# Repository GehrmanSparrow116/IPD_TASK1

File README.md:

# IPD_TASK1 BY GROUP 28

E077-Sarvesh Hedulkar

E076-Tanish Hangloo

E070-Chaitanya Deorukhkar

E079-Aadit Rajbhar

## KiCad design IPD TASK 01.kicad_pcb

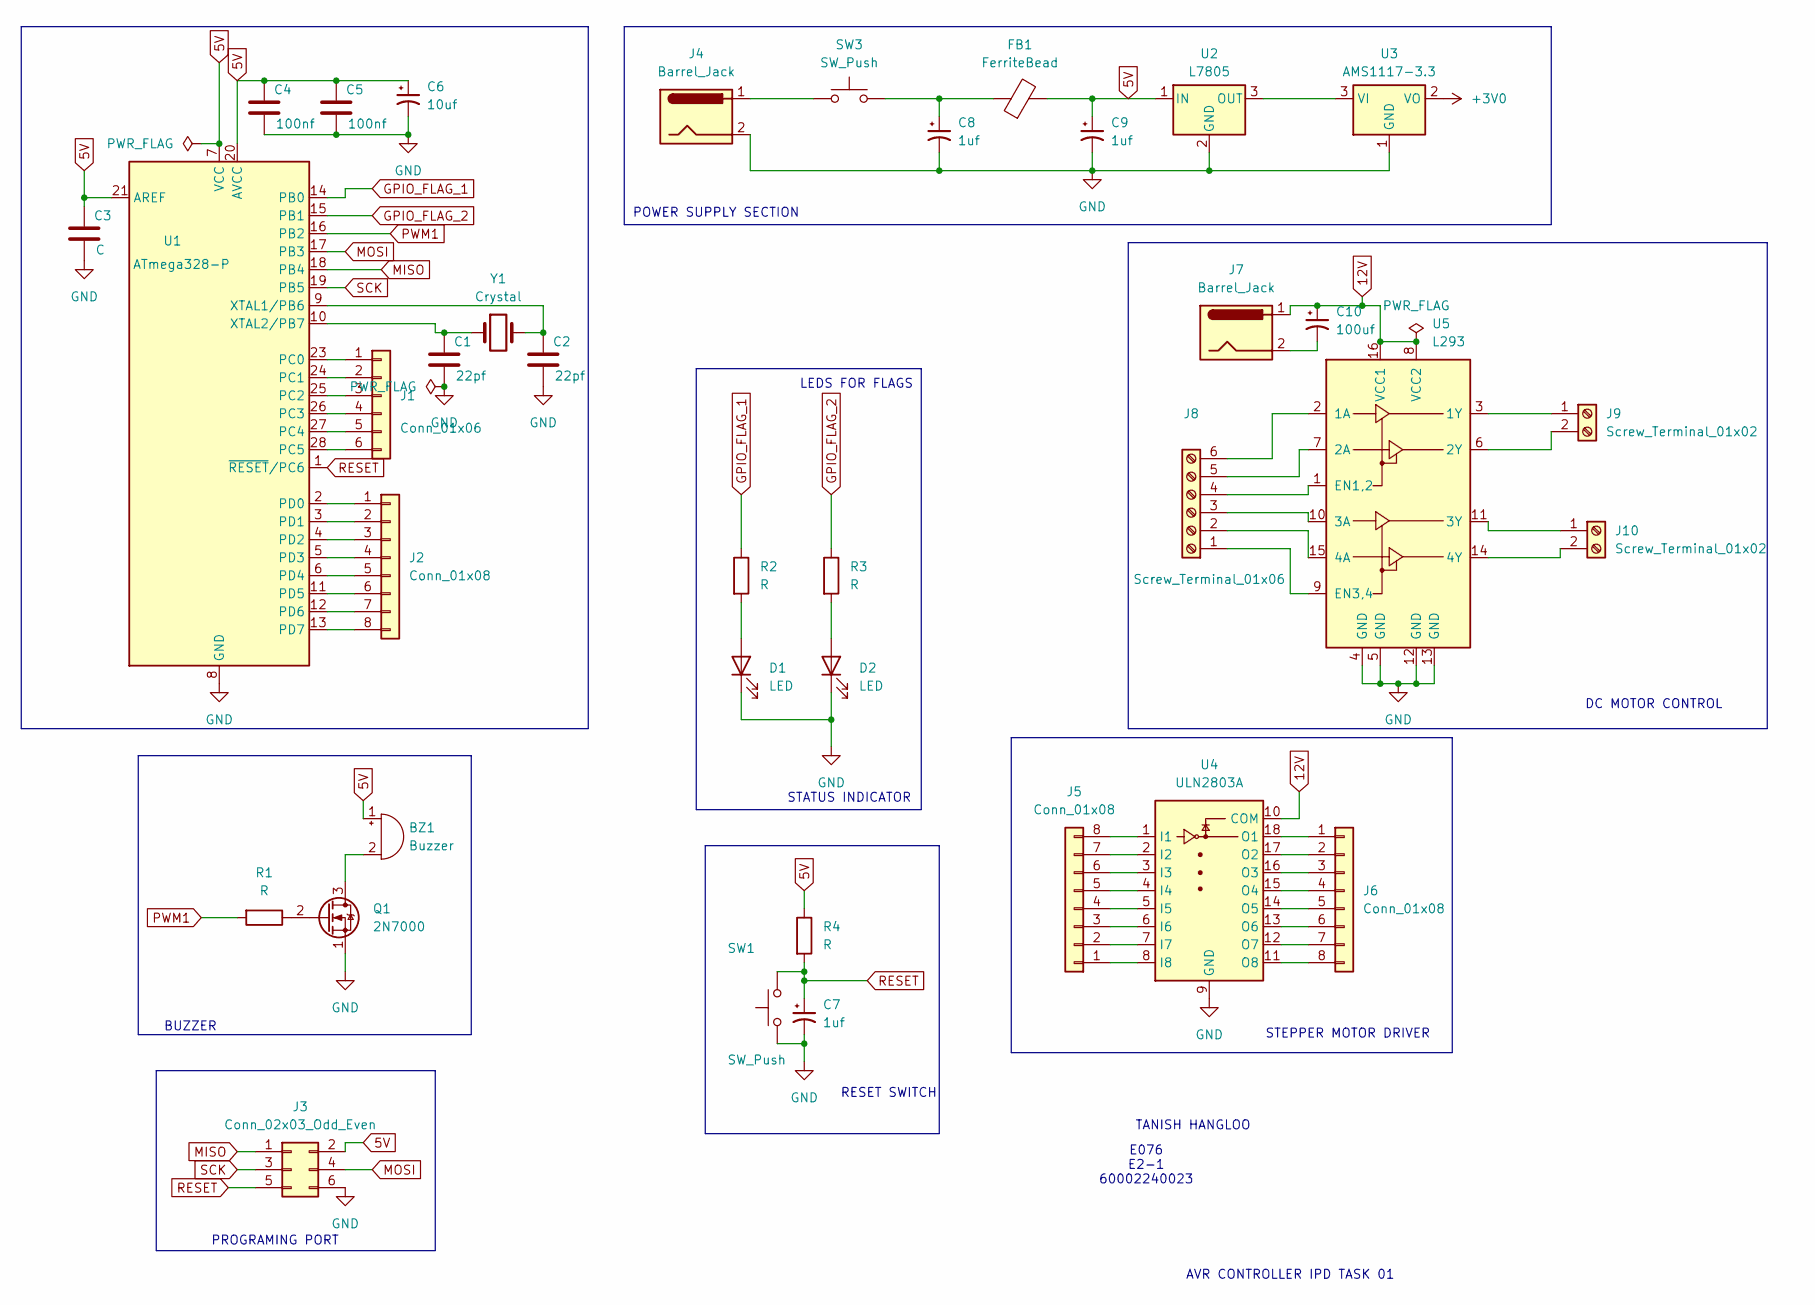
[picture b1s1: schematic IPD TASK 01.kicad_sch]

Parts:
BZ1: Buzzer; PinHeader_1x02_P2.54mm_Vertical
C1, C2: 22pf; C_Disc_D5.0mm_W2.5mm_P5.00mm
C3: C; C_Disc_D5.0mm_W2.5mm_P5.00mm
C4, C5: 100nf; CP_Radial_D5.0mm_P2.50mm
C6: 10uf; CP_Radial_D5.0mm_P2.50mm
C7, C8, C9: 1uf; C_Disc_D5.0mm_W2.5mm_P5.00mm
C10: 100uf; C_Disc_D5.0mm_W2.5mm_P5.00mm
D1, D2: LED; LED_D5.0mm
FB1: FerriteBead; R_Axial_DIN0207_L6.3mm_D2.5mm_P7.62mm_Horizontal
J1: Conn_01x06; PinHeader_1x06_P2.54mm_Vertical
J2, J5, J6: Conn_01x08; PinHeader_1x08_P2.54mm_Vertical
J3: Conn_02x03_Odd_Even; PinHeader_2x03_P2.54mm_Vertical
J4: Barrel_Jack; PinHeader_1x02_P2.54mm_Vertical
J7: Barrel_Jack; TerminalBlock_Phoenix_PT-1,5-2-5.0-H_1x02_P5.00mm_Horizontal
J8: Screw_Terminal_01x06; PinHeader_1x06_P2.54mm_Vertical
J9, J10: Screw_Terminal_01x02; PinHeader_1x02_P2.54mm_Vertical
Q1: 2N7000; TO-92_Inline
R1, R2, R3, R4: R; R_Axial_DIN0207_L6.3mm_D2.5mm_P15.24mm_Horizontal
SW1, SW3: SW_Push; PinHeader_1x02_P2.54mm_Vertical
U1: ATmega328-P; DIP-28_W7.62mm
U2: L7805; TO-220-3_Vertical
U3: AMS1117-3.3; SOT-223-3_TabPin2
U4: ULN2803A; DIP-18_W7.62mm
U5: L293; DIP-16_W7.62mm
Y1: Crystal; Crystal_HC49-U_Vertical

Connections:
5V: BZ1.1 (+), C3.1, C4.1, C5.1, C6.1, C9.1, FB1.2, J3.2, R4.1, U1.7 (VCC), U1.20 (AVCC), U1.21 (AREF), U2.1 (IN)
12V: C10.1, J7.1, U4.10 (COM), U5.8 (VCC2), U5.16 (VCC1)
+3V0: U3.2 (VO)
GND: C1.2, C2.2, C3.2, C4.2, C5.2, C6.2, C7.2, C8.2, C9.2, D1.1 (K), D2.1 (K), J3.6, J4.2, Q1.1 (S), SW1.1, U1.8 (GND), U1.22 (GND), U2.2 (GND), U3.1 (GND), U4.9 (GND), U5.4 (GND), U5.5 (GND), U5.12 (GND), U5.13 (GND)
GPIO_FLAG_1: R2.1, U1.14 (PB0)
GPIO_FLAG_2: R3.1, U1.15 (PB1)
MISO: J3.1, U1.18 (PB4)
MOSI: J3.4, U1.17 (PB3)
unnamed: BZ1.2 (-), Q1.3 (D)
unnamed: C8.1, FB1.1, SW3.2
unnamed: C10.2, J7.2
unnamed: D1.2 (A), R2.2
unnamed: D2.2 (A), R3.2
unnamed: J1.1, U1.23 (PC0)
unnamed: J1.2, U1.24 (PC1)
unnamed: J1.3, U1.25 (PC2)
unnamed: J1.4, U1.26 (PC3)
unnamed: J1.5, U1.27 (PC4)
unnamed: J1.6, U1.28 (PC5)
unnamed: J2.1, U1.2 (PD0)
unnamed: J2.2, U1.3 (PD1)
unnamed: J2.3, U1.4 (PD2)
unnamed: J2.4, U1.5 (PD3)
unnamed: J2.5, U1.6 (PD4)
unnamed: J2.6, U1.11 (PD5)
unnamed: J2.7, U1.12 (PD6)
unnamed: J2.8, U1.13 (PD7)
unnamed: J4.1, SW3.1
unnamed: J5.1, U4.8 (I8)
unnamed: J5.2, U4.7 (I7)
unnamed: J5.3, U4.6 (I6)
unnamed: J5.4, U4.5 (I5)
unnamed: J5.5, U4.4 (I4)
unnamed: J5.6, U4.3 (I3)
unnamed: J5.7, U4.2 (I2)
unnamed: J5.8, U4.1 (I1)
unnamed: J6.1, U4.18 (O1)
unnamed: J6.2, U4.17 (O2)
unnamed: J6.3, U4.16 (O3)
unnamed: J6.4, U4.15 (O4)
unnamed: J6.5, U4.14 (O5)
unnamed: J6.6, U4.13 (O6)
unnamed: J6.7, U4.12 (O7)
unnamed: J6.8, U4.11 (O8)
unnamed: J8.1, U5.9 (EN3,4)
unnamed: J8.2, U5.15 (4A)
unnamed: J8.3, U5.10 (3A)
unnamed: J8.4, U5.1 (EN1,2)
unnamed: J8.5, U5.7 (2A)
unnamed: J8.6, U5.2 (1A)
unnamed: J9.1, U5.3 (1Y)
unnamed: J9.2, U5.6 (2Y)
unnamed: J10.1, U5.11 (3Y)
unnamed: J10.2, U5.14 (4Y)
unnamed: Q1.2 (G), R1.1
unnamed: C2.1, U1.9 (XTAL1/PB6), Y1.2
unnamed: C1.1, U1.10 (XTAL2/PB7), Y1.1
unnamed: U2.3 (OUT), U3.3 (VI)
PWM1: R1.2, U1.16 (PB2)
RESET: C7.1, J3.5, R4.2, SW1.2, U1.1 (~RESET/PC6)
SCK: J3.3, U1.19 (PB5)

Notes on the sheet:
PROGRAMING PORT
DC MOTOR CONTROL
BUZZER
AVR CONTROLLER IPD TASK 01
RESET SWITCH
STEPPER MOTOR DRIVER
STATUS INDICATOR
POWER SUPPLY SECTION
LEDS FOR FLAGS
TANISH HANGLOO
E076 E2-1 60002240023

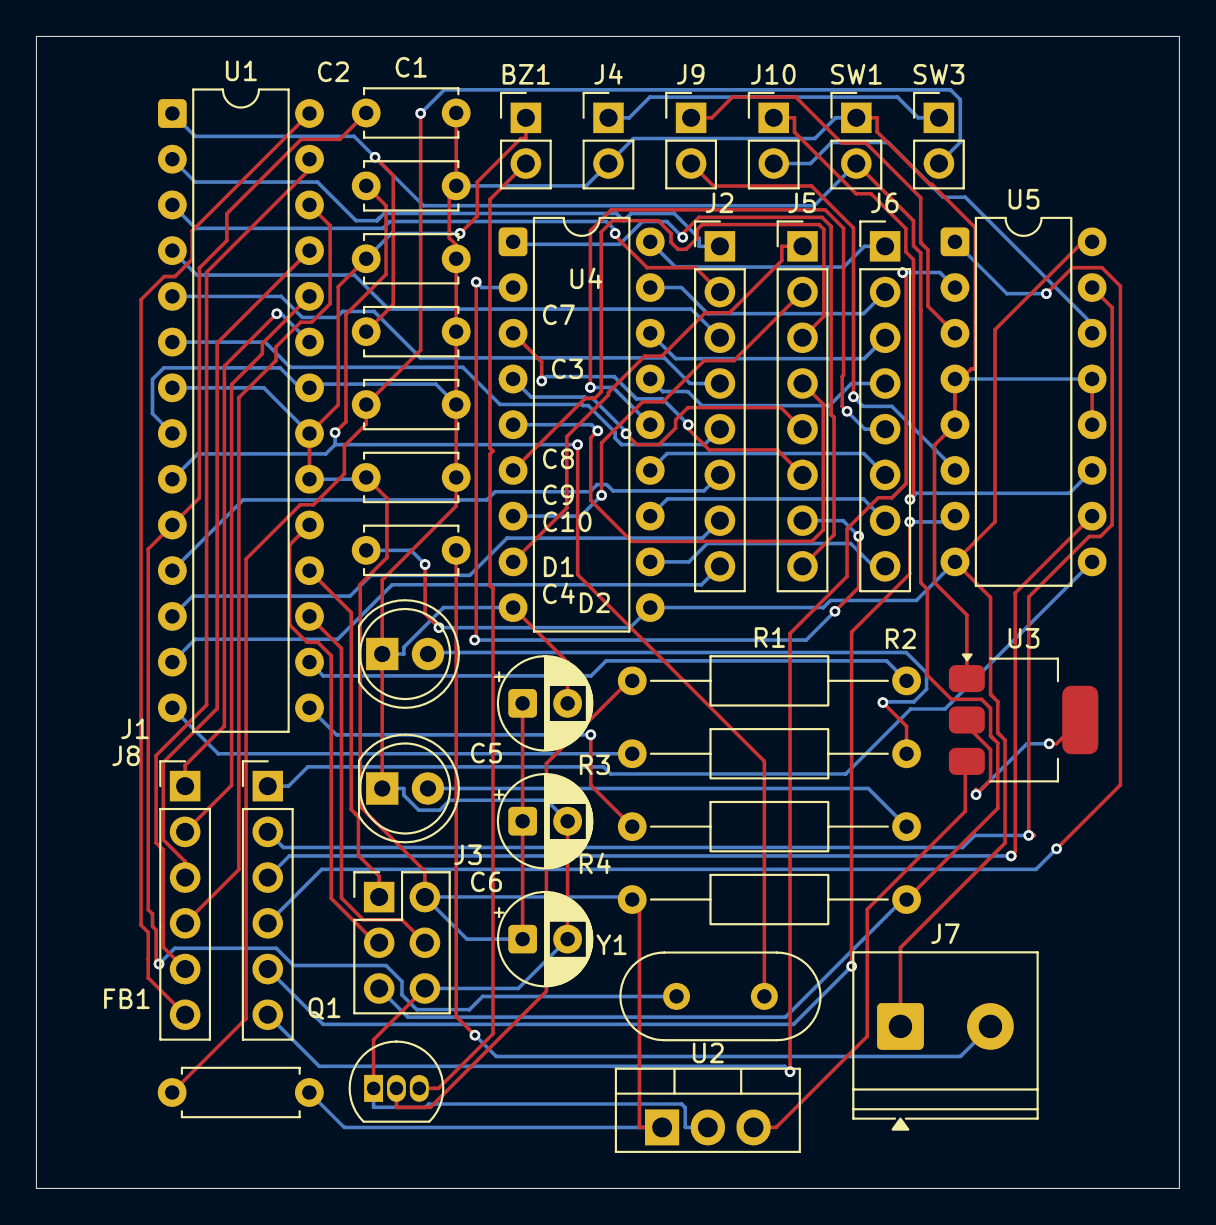
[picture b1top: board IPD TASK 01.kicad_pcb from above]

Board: 2 copper layers, 63.5 x 64.0 mm, 37 parts (0 on the bottom side), 60 nets.

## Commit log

2026-02-28 Update project title in README
2026-02-28 Add group members to README
